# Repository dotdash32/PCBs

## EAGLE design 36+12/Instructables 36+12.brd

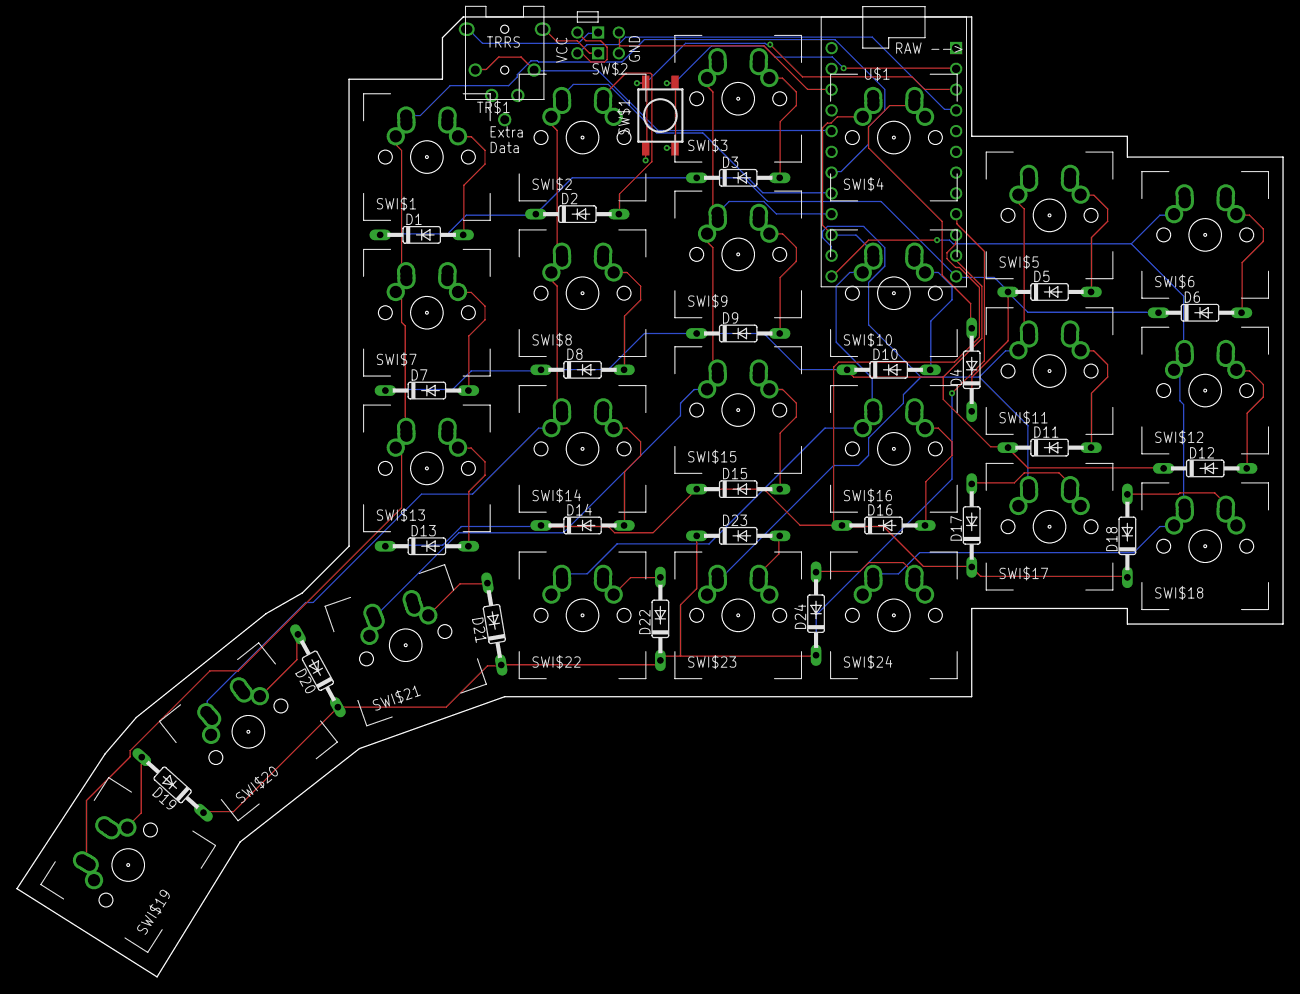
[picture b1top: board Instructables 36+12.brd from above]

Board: 2 copper layers, 154.9 x 117.5 mm, 52 parts (0 on the bottom side), 41 nets.

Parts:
D1, D2, D3, D4, D5, D6, D7, D8, D9, D10, D11, D12, D13, D14, D15, D16, D17, D18, D19, D20, D21, D22, D23, D24: 1N4148DO35-10; DO35-10
SW$1: RSTSWSMD; FLATSWT
SW$2: TRANSFERHOLEY; TRANSFER
SWI$1, SWI$2, SWI$3, SWI$4, SWI$5, SWI$6, SWI$7, SWI$8, SWI$9, SWI$10, SWI$11, SWI$12, SWI$13, SWI$14, SWI$15, SWI$16, SWI$17, SWI$18, SWI$19, SWI$20, SWI$21, SWI$22, SWI$23, SWI$24: MX/ALPSDOUBLESIDED; DOUBLED_MX/ALPS
TR$1: TRRSJACK
U$1: PROMICROUNDER; PROMICRO_UNDER

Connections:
unnamed: D13.A, SWI$13.RAL, SWI$13.RAR, SWI$13.RCL, SWI$13.RCR
unnamed: D1.A, SWI$1.RAL, SWI$1.RAR, SWI$1.RCL, SWI$1.RCR
unnamed: D2.A, SWI$2.RAL, SWI$2.RAR, SWI$2.RCL, SWI$2.RCR
unnamed: D3.A, SWI$3.RAL, SWI$3.RAR, SWI$3.RCL, SWI$3.RCR
unnamed: D4.A, SWI$4.RAL, SWI$4.RAR, SWI$4.RCL, SWI$4.RCR
unnamed: D5.A, SWI$5.RAL, SWI$5.RAR, SWI$5.RCL, SWI$5.RCR
unnamed: D6.A, SWI$6.RAL, SWI$6.RAR, SWI$6.RCL, SWI$6.RCR
unnamed: D7.A, SWI$7.RAL, SWI$7.RAR, SWI$7.RCL, SWI$7.RCR
unnamed: D8.A, SWI$8.RAL, SWI$8.RAR, SWI$8.RCL, SWI$8.RCR
unnamed: D9.A, SWI$9.RAL, SWI$9.RAR, SWI$9.RCL, SWI$9.RCR
unnamed: D10.A, SWI$10.RAL, SWI$10.RAR, SWI$10.RCL, SWI$10.RCR
unnamed: D11.A, SWI$11.RAL, SWI$11.RAR, SWI$11.RCL, SWI$11.RCR
unnamed: D12.A, SWI$12.RAL, SWI$12.RAR, SWI$12.RCL, SWI$12.RCR
unnamed: D14.A, SWI$14.RAL, SWI$14.RAR, SWI$14.RCL, SWI$14.RCR
unnamed: D15.A, SWI$15.RAL, SWI$15.RAR, SWI$15.RCL, SWI$15.RCR
unnamed: D16.A, SWI$16.RAL, SWI$16.RAR, SWI$16.RCL, SWI$16.RCR
unnamed: D17.A, SWI$17.RAL, SWI$17.RAR, SWI$17.RCL, SWI$17.RCR
unnamed: D18.A, SWI$18.RAL, SWI$18.RAR, SWI$18.RCL, SWI$18.RCR
unnamed: D19.A, SWI$19.RAL, SWI$19.RAR, SWI$19.RCL, SWI$19.RCR
unnamed: D20.A, SWI$20.RAL, SWI$20.RAR, SWI$20.RCL, SWI$20.RCR
unnamed: D21.A, SWI$21.RAL, SWI$21.RAR, SWI$21.RCL, SWI$21.RCR
unnamed: D22.A, SWI$22.RAL, SWI$22.RAR, SWI$22.RCL, SWI$22.RCR
unnamed: D23.A, SWI$23.RAL, SWI$23.RAR, SWI$23.RCL, SWI$23.RCR
unnamed: D24.A, SWI$24.RAL, SWI$24.RAR, SWI$24.RCL, SWI$24.RCR
unnamed: D1.C, D2.C, D3.C, D4.C, D5.C, D6.C, U$1.P$13
unnamed: D7.C, D8.C, D9.C, D10.C, D11.C, D12.C, U$1.P$14
unnamed: D13.C, D14.C, D15.C, D16.C, D17.C, D18.C, U$1.P$15
unnamed: D19.C, D20.C, D21.C, D22.C, D23.C, D24.C, U$1.P$16
unnamed: SWI$1.LAL, SWI$1.LAR, SWI$1.LCL, SWI$1.LCR, SWI$7.LAL, SWI$7.LAR, SWI$7.LCL, SWI$7.LCR, SWI$13.LAL, SWI$13.LAR, SWI$13.LCL, SWI$13.LCR, SWI$19.LAL, SWI$19.LAR, SWI$19.LCL, SWI$19.LCR, U$1.P$7
unnamed: SWI$2.LAL, SWI$2.LAR, SWI$2.LCL, SWI$2.LCR, SWI$8.LAL, SWI$8.LAR, SWI$8.LCL, SWI$8.LCR, SWI$14.LAL, SWI$14.LAR, SWI$14.LCL, SWI$14.LCR, SWI$20.LAL, SWI$20.LAR, SWI$20.LCL, SWI$20.LCR, U$1.P$8
unnamed: SWI$3.LAL, SWI$3.LAR, SWI$3.LCL, SWI$3.LCR, SWI$9.LAL, SWI$9.LAR, SWI$9.LCL, SWI$9.LCR, SWI$15.LAL, SWI$15.LAR, SWI$15.LCL, SWI$15.LCR, SWI$21.LAL, SWI$21.LAR, SWI$21.LCL, SWI$21.LCR, U$1.P$9
unnamed: SWI$4.LAL, SWI$4.LAR, SWI$4.LCL, SWI$4.LCR, SWI$10.LAL, SWI$10.LAR, SWI$10.LCL, SWI$10.LCR, SWI$16.LAL, SWI$16.LAR, SWI$16.LCL, SWI$16.LCR, SWI$22.LAL, SWI$22.LAR, SWI$22.LCL, SWI$22.LCR, U$1.P$10
unnamed: SWI$5.LAL, SWI$5.LAR, SWI$5.LCL, SWI$5.LCR, SWI$11.LAL, SWI$11.LAR, SWI$11.LCL, SWI$11.LCR, SWI$17.LAL, SWI$17.LAR, SWI$17.LCL, SWI$17.LCR, SWI$23.LAL, SWI$23.LAR, SWI$23.LCL, SWI$23.LCR, U$1.P$11
unnamed: SWI$6.LAL, SWI$6.LAR, SWI$6.LCL, SWI$6.LCR, SWI$12.LAL, SWI$12.LAR, SWI$12.LCL, SWI$12.LCR, SWI$18.LAL, SWI$18.LAR, SWI$18.LCL, SWI$18.LCR, SWI$24.LAL, SWI$24.LAR, SWI$24.LCL, SWI$24.LCR, U$1.P$12
unnamed: SW$1.P$1, SW$1.P$2, SW$1.P$5, SW$1.P$6, U$1.P$23
unnamed: SW$1.P$3, SW$1.P$4, SW$1.P$7, SW$1.P$8, U$1.P$22
unnamed: SW$2.GND1, SW$2.GND2, U$1.P$3
unnamed: SW$2.VCC1, SW$2.VCC2, U$1.P$21
unnamed: SW$2.IN1, TR$1.1B, TR$1.1T
unnamed: SW$2.IN4, TR$1.4B, TR$1.4T
unnamed: TR$1.2B, TR$1.2T, U$1.P$5

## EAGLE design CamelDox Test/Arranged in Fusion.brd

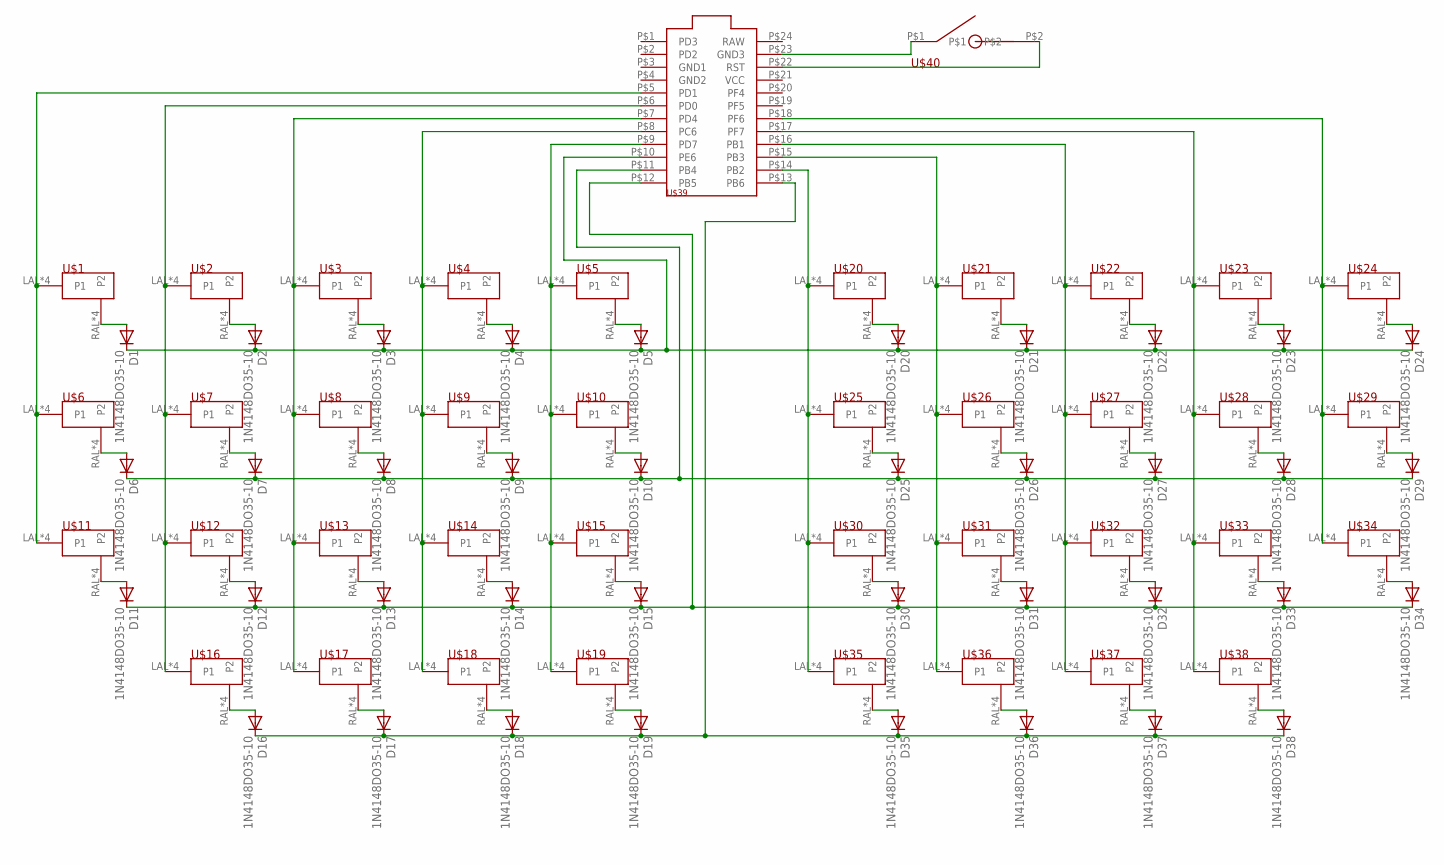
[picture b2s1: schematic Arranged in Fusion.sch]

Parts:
D1, D2, D3, D4, D5, D6, D7, D8, D9, D10, D11, D12, D13, D14, D15, D16, D17, D18, D19, D20, D21, D22, D23, D24, D25, D26, D27, D28, D29, D30, D31, D32, D33, D34, D35, D36, D37, D38: 1N4148DO35-10; DO35-10
U$1, U$2, U$3, U$4, U$5, U$6, U$7, U$8, U$9, U$10, U$11, U$12, U$13, U$14, U$15, U$16, U$17, U$18, U$19, U$20, U$21, U$22, U$23, U$24, U$25, U$26, U$27, U$28, U$29, U$30, U$31, U$32, U$33, U$34, U$35, U$36, U$37, U$38: MANDOUBLEONESIDED; MX/ALPS
U$39: PROMICRO
U$40: RSTSW; SKHL

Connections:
unnamed: D1.A, U$1.RAL (P2), U$1.RAR (P2), U$1.RCL (P2), U$1.RCR (P2)
unnamed: D2.A, U$2.RAL (P2), U$2.RAR (P2), U$2.RCL (P2), U$2.RCR (P2)
unnamed: D3.A, U$3.RAL (P2), U$3.RAR (P2), U$3.RCL (P2), U$3.RCR (P2)
unnamed: D4.A, U$4.RAL (P2), U$4.RAR (P2), U$4.RCL (P2), U$4.RCR (P2)
unnamed: D5.A, U$5.RAL (P2), U$5.RAR (P2), U$5.RCL (P2), U$5.RCR (P2)
unnamed: D1.C, D2.C, D3.C, D4.C, D5.C, D20.C, D21.C, D22.C, D23.C, D24.C, U$39.P$10 (PE6)
unnamed: D6.A, U$6.RAL (P2), U$6.RAR (P2), U$6.RCL (P2), U$6.RCR (P2)
unnamed: D7.A, U$7.RAL (P2), U$7.RAR (P2), U$7.RCL (P2), U$7.RCR (P2)
unnamed: D8.A, U$8.RAL (P2), U$8.RAR (P2), U$8.RCL (P2), U$8.RCR (P2)
unnamed: D9.A, U$9.RAL (P2), U$9.RAR (P2), U$9.RCL (P2), U$9.RCR (P2)
unnamed: D10.A, U$10.RAL (P2), U$10.RAR (P2), U$10.RCL (P2), U$10.RCR (P2)
unnamed: D11.A, U$11.RAL (P2), U$11.RAR (P2), U$11.RCL (P2), U$11.RCR (P2)
unnamed: D12.A, U$12.RAL (P2), U$12.RAR (P2), U$12.RCL (P2), U$12.RCR (P2)
unnamed: D13.A, U$13.RAL (P2), U$13.RAR (P2), U$13.RCL (P2), U$13.RCR (P2)
unnamed: D14.A, U$14.RAL (P2), U$14.RAR (P2), U$14.RCL (P2), U$14.RCR (P2)
unnamed: D15.A, U$15.RAL (P2), U$15.RAR (P2), U$15.RCL (P2), U$15.RCR (P2)
unnamed: D11.C, D12.C, D13.C, D14.C, D15.C, D30.C, D31.C, D32.C, D33.C, D34.C, U$39.P$12 (PB5)
unnamed: D16.A, U$16.RAL (P2), U$16.RAR (P2), U$16.RCL (P2), U$16.RCR (P2)
unnamed: D17.A, U$17.RAL (P2), U$17.RAR (P2), U$17.RCL (P2), U$17.RCR (P2)
unnamed: D18.A, U$18.RAL (P2), U$18.RAR (P2), U$18.RCL (P2), U$18.RCR (P2)
unnamed: D19.A, U$19.RAL (P2), U$19.RAR (P2), U$19.RCL (P2), U$19.RCR (P2)
unnamed: D16.C, D17.C, D18.C, D19.C, D35.C, D36.C, D37.C, D38.C, U$39.P$13 (PB6)
unnamed: D20.A, U$20.RAL (P2), U$20.RAR (P2), U$20.RCL (P2), U$20.RCR (P2)
unnamed: D21.A, U$21.RAL (P2), U$21.RAR (P2), U$21.RCL (P2), U$21.RCR (P2)
unnamed: D22.A, U$22.RAL (P2), U$22.RAR (P2), U$22.RCL (P2), U$22.RCR (P2)
unnamed: D23.A, U$23.RAL (P2), U$23.RAR (P2), U$23.RCL (P2), U$23.RCR (P2)
unnamed: D24.A, U$24.RAL (P2), U$24.RAR (P2), U$24.RCL (P2), U$24.RCR (P2)
unnamed: D25.A, U$25.RAL (P2), U$25.RAR (P2), U$25.RCL (P2), U$25.RCR (P2)
unnamed: D26.A, U$26.RAL (P2), U$26.RAR (P2), U$26.RCL (P2), U$26.RCR (P2)
unnamed: D27.A, U$27.RAL (P2), U$27.RAR (P2), U$27.RCL (P2), U$27.RCR (P2)
unnamed: D28.A, U$28.RAL (P2), U$28.RAR (P2), U$28.RCL (P2), U$28.RCR (P2)
unnamed: D29.A, U$29.RAL (P2), U$29.RAR (P2), U$29.RCL (P2), U$29.RCR (P2)
unnamed: D30.A, U$30.RAL (P2), U$30.RAR (P2), U$30.RCL (P2), U$30.RCR (P2)
unnamed: D31.A, U$31.RAL (P2), U$31.RAR (P2), U$31.RCL (P2), U$31.RCR (P2)
unnamed: D32.A, U$32.RAL (P2), U$32.RAR (P2), U$32.RCL (P2), U$32.RCR (P2)
unnamed: D33.A, U$33.RAL (P2), U$33.RAR (P2), U$33.RCL (P2), U$33.RCR (P2)
unnamed: D34.A, U$34.RAL (P2), U$34.RAR (P2), U$34.RCL (P2), U$34.RCR (P2)
unnamed: D35.A, U$35.RAL (P2), U$35.RAR (P2), U$35.RCL (P2), U$35.RCR (P2)
unnamed: D36.A, U$36.RAL (P2), U$36.RAR (P2), U$36.RCL (P2), U$36.RCR (P2)
unnamed: D37.A, U$37.RAL (P2), U$37.RAR (P2), U$37.RCL (P2), U$37.RCR (P2)
unnamed: D38.A, U$38.RAL (P2), U$38.RAR (P2), U$38.RCL (P2), U$38.RCR (P2)
unnamed: D6.C, D7.C, D8.C, D9.C, D10.C, D25.C, D26.C, D27.C, D28.C, D29.C, U$39.P$11 (PB4)
unnamed: U$1.LAL (P1), U$1.LAR (P1), U$1.LCL (P1), U$1.LCR (P1), U$6.LAL (P1), U$6.LAR (P1), U$6.LCL (P1), U$6.LCR (P1), U$11.LAL (P1), U$11.LAR (P1), U$11.LCL (P1), U$11.LCR (P1), U$39.P$5 (PD1)
unnamed: U$2.LAL (P1), U$2.LAR (P1), U$2.LCL (P1), U$2.LCR (P1), U$7.LAL (P1), U$7.LAR (P1), U$7.LCL (P1), U$7.LCR (P1), U$12.LAL (P1), U$12.LAR (P1), U$12.LCL (P1), U$12.LCR (P1), U$16.LAL (P1), U$16.LAR (P1), U$16.LCL (P1), U$16.LCR (P1), U$39.P$6 (PD0)
unnamed: U$3.LAL (P1), U$3.LAR (P1), U$3.LCL (P1), U$3.LCR (P1), U$8.LAL (P1), U$8.LAR (P1), U$8.LCL (P1), U$8.LCR (P1), U$13.LAL (P1), U$13.LAR (P1), U$13.LCL (P1), U$13.LCR (P1), U$17.LAL (P1), U$17.LAR (P1), U$17.LCL (P1), U$17.LCR (P1), U$39.P$7 (PD4)
unnamed: U$4.LAL (P1), U$4.LAR (P1), U$4.LCL (P1), U$4.LCR (P1), U$9.LAL (P1), U$9.LAR (P1), U$9.LCL (P1), U$9.LCR (P1), U$14.LAL (P1), U$14.LAR (P1), U$14.LCL (P1), U$14.LCR (P1), U$18.LAL (P1), U$18.LAR (P1), U$18.LCL (P1), U$18.LCR (P1), U$39.P$8 (PC6)
unnamed: U$5.LAL (P1), U$5.LAR (P1), U$5.LCL (P1), U$5.LCR (P1), U$10.LAL (P1), U$10.LAR (P1), U$10.LCL (P1), U$10.LCR (P1), U$15.LAL (P1), U$15.LAR (P1), U$15.LCL (P1), U$15.LCR (P1), U$19.LAL (P1), U$19.LAR (P1), U$19.LCL (P1), U$19.LCR (P1), U$39.P$9 (PD7)
unnamed: U$20.LAL (P1), U$20.LAR (P1), U$20.LCL (P1), U$20.LCR (P1), U$25.LAL (P1), U$25.LAR (P1), U$25.LCL (P1), U$25.LCR (P1), U$30.LAL (P1), U$30.LAR (P1), U$30.LCL (P1), U$30.LCR (P1), U$35.LAL (P1), U$35.LAR (P1), U$35.LCL (P1), U$35.LCR (P1), U$39.P$14 (PB2)
unnamed: U$21.LAL (P1), U$21.LAR (P1), U$21.LCL (P1), U$21.LCR (P1), U$26.LAL (P1), U$26.LAR (P1), U$26.LCL (P1), U$26.LCR (P1), U$31.LAL (P1), U$31.LAR (P1), U$31.LCL (P1), U$31.LCR (P1), U$36.LAL (P1), U$36.LAR (P1), U$36.LCL (P1), U$36.LCR (P1), U$39.P$15 (PB3)
unnamed: U$22.LAL (P1), U$22.LAR (P1), U$22.LCL (P1), U$22.LCR (P1), U$27.LAL (P1), U$27.LAR (P1), U$27.LCL (P1), U$27.LCR (P1), U$32.LAL (P1), U$32.LAR (P1), U$32.LCL (P1), U$32.LCR (P1), U$37.LAL (P1), U$37.LAR (P1), U$37.LCL (P1), U$37.LCR (P1), U$39.P$16 (PB1)
unnamed: U$23.LAL (P1), U$23.LAR (P1), U$23.LCL (P1), U$23.LCR (P1), U$28.LAL (P1), U$28.LAR (P1), U$28.LCL (P1), U$28.LCR (P1), U$33.LAL (P1), U$33.LAR (P1), U$33.LCL (P1), U$33.LCR (P1), U$38.LAL (P1), U$38.LAR (P1), U$38.LCL (P1), U$38.LCR (P1), U$39.P$17 (PF7)
unnamed: U$24.LAL (P1), U$24.LAR (P1), U$24.LCL (P1), U$24.LCR (P1), U$29.LAL (P1), U$29.LAR (P1), U$29.LCL (P1), U$29.LCR (P1), U$34.LAL (P1), U$34.LAR (P1), U$34.LCL (P1), U$34.LCR (P1), U$39.P$18 (PF6)
unnamed: U$39.P$23 (GND3), U$40.P$1
unnamed: U$39.P$22 (RST), U$40.P$2

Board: 2 copper layers, 78 parts (0 on the bottom side), 54 nets, no tracks yet.

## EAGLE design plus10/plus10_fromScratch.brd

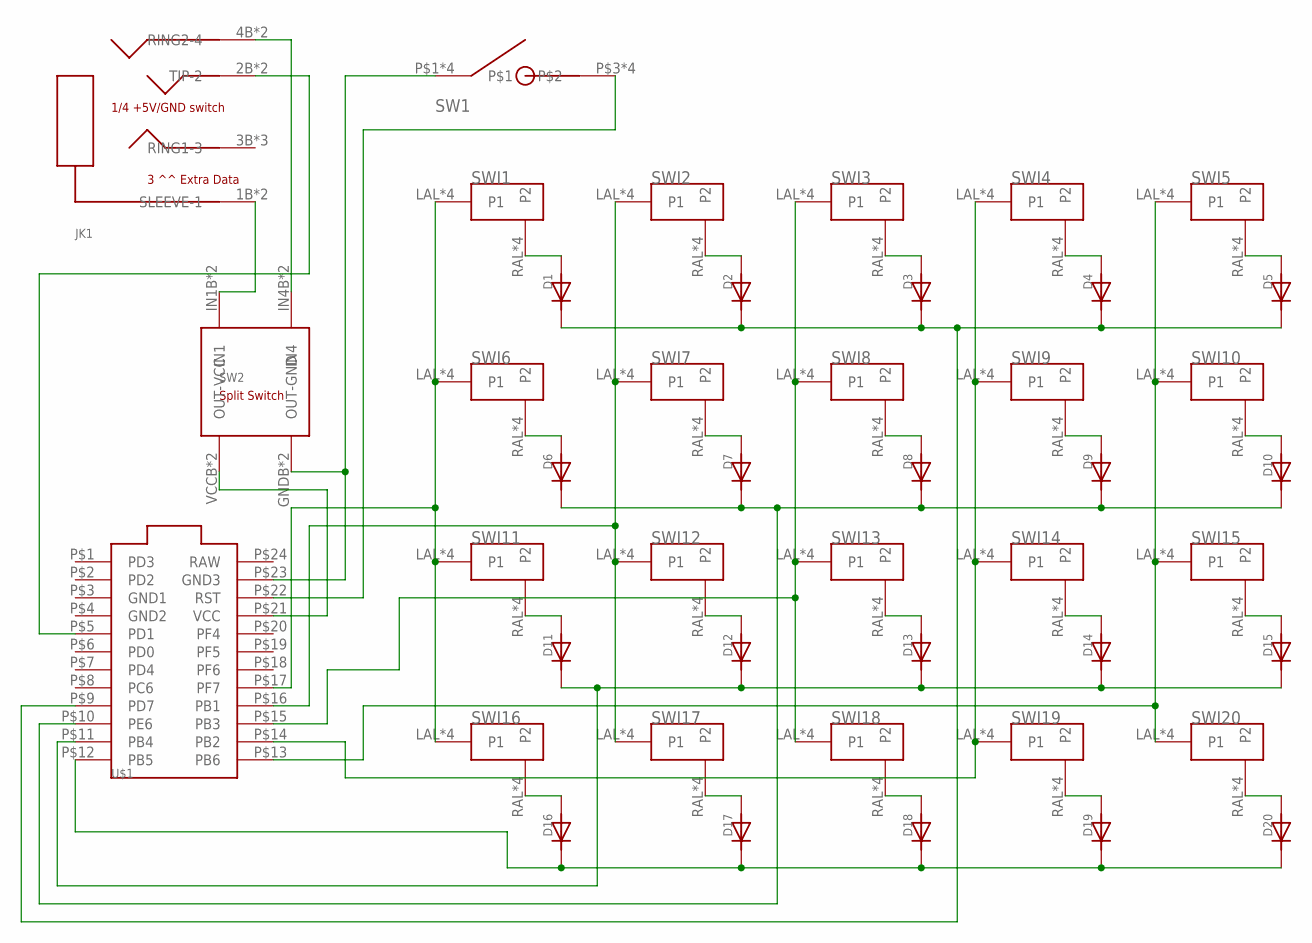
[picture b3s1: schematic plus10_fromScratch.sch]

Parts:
D1, D2, D3, D4, D5, D6, D7, D8, D9, D10, D11, D12, D13, D14, D15, D16, D17, D18, D19, D20: DIODE; DIODE_COMBO
JK1: TRRSJACK
SW1: RSTSWSMD; FLATSWT
SW2: TRANSFERPADDY; TRANSFER_PADS
SWI1, SWI2, SWI3, SWI4, SWI5, SWI6, SWI7, SWI8, SWI9, SWI10, SWI11, SWI12, SWI13, SWI14, SWI15, SWI16, SWI17, SWI18, SWI19, SWI20: MX/ALPSDOUBLESIDED; DOUBLED_MX/ALPS
U$1: PROMICROUNDER; PROMICRO_UNDER

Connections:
unnamed: D1.ANOSB (AN), D1.ANOST (AN), D1.ANOT (AN), SWI1.RAL (P2), SWI1.RAR (P2), SWI1.RCL (P2), SWI1.RCR (P2)
unnamed: SWI4.LAL (P1), SWI4.LAR (P1), SWI4.LCL (P1), SWI4.LCR (P1), SWI9.LAL (P1), SWI9.LAR (P1), SWI9.LCL (P1), SWI9.LCR (P1), SWI14.LAL (P1), SWI14.LAR (P1), SWI14.LCL (P1), SWI14.LCR (P1), SWI19.LAL (P1), SWI19.LAR (P1), SWI19.LCL (P1), SWI19.LCR (P1), U$1.P$14 (PB2)
unnamed: SWI3.LAL (P1), SWI3.LAR (P1), SWI3.LCL (P1), SWI3.LCR (P1), SWI8.LAL (P1), SWI8.LAR (P1), SWI8.LCL (P1), SWI8.LCR (P1), SWI13.LAL (P1), SWI13.LAR (P1), SWI13.LCL (P1), SWI13.LCR (P1), SWI18.LAL (P1), SWI18.LAR (P1), SWI18.LCL (P1), SWI18.LCR (P1), U$1.P$15 (PB3)
unnamed: SWI5.LAL (P1), SWI5.LAR (P1), SWI5.LCL (P1), SWI5.LCR (P1), SWI10.LAL (P1), SWI10.LAR (P1), SWI10.LCL (P1), SWI10.LCR (P1), SWI15.LAL (P1), SWI15.LAR (P1), SWI15.LCL (P1), SWI15.LCR (P1), SWI20.LAL (P1), SWI20.LAR (P1), SWI20.LCL (P1), SWI20.LCR (P1), U$1.P$13 (PB6)
unnamed: D2.ANOSB (AN), D2.ANOST (AN), D2.ANOT (AN), SWI2.RAL (P2), SWI2.RAR (P2), SWI2.RCL (P2), SWI2.RCR (P2)
unnamed: D3.ANOSB (AN), D3.ANOST (AN), D3.ANOT (AN), SWI3.RAL (P2), SWI3.RAR (P2), SWI3.RCL (P2), SWI3.RCR (P2)
unnamed: D4.ANOSB (AN), D4.ANOST (AN), D4.ANOT (AN), SWI4.RAL (P2), SWI4.RAR (P2), SWI4.RCL (P2), SWI4.RCR (P2)
unnamed: D5.ANOSB (AN), D5.ANOST (AN), D5.ANOT (AN), SWI5.RAL (P2), SWI5.RAR (P2), SWI5.RCL (P2), SWI5.RCR (P2)
unnamed: D6.ANOSB (AN), D6.ANOST (AN), D6.ANOT (AN), SWI6.RAL (P2), SWI6.RAR (P2), SWI6.RCL (P2), SWI6.RCR (P2)
unnamed: D7.ANOSB (AN), D7.ANOST (AN), D7.ANOT (AN), SWI7.RAL (P2), SWI7.RAR (P2), SWI7.RCL (P2), SWI7.RCR (P2)
unnamed: D8.ANOSB (AN), D8.ANOST (AN), D8.ANOT (AN), SWI8.RAL (P2), SWI8.RAR (P2), SWI8.RCL (P2), SWI8.RCR (P2)
unnamed: D9.ANOSB (AN), D9.ANOST (AN), D9.ANOT (AN), SWI9.RAL (P2), SWI9.RAR (P2), SWI9.RCL (P2), SWI9.RCR (P2)
unnamed: D10.ANOSB (AN), D10.ANOST (AN), D10.ANOT (AN), SWI10.RAL (P2), SWI10.RAR (P2), SWI10.RCL (P2), SWI10.RCR (P2)
unnamed: D11.ANOSB (AN), D11.ANOST (AN), D11.ANOT (AN), SWI11.RAL (P2), SWI11.RAR (P2), SWI11.RCL (P2), SWI11.RCR (P2)
unnamed: D12.ANOSB (AN), D12.ANOST (AN), D12.ANOT (AN), SWI12.RAL (P2), SWI12.RAR (P2), SWI12.RCL (P2), SWI12.RCR (P2)
unnamed: D13.ANOSB (AN), D13.ANOST (AN), D13.ANOT (AN), SWI13.RAL (P2), SWI13.RAR (P2), SWI13.RCL (P2), SWI13.RCR (P2)
unnamed: D14.ANOSB (AN), D14.ANOST (AN), D14.ANOT (AN), SWI14.RAL (P2), SWI14.RAR (P2), SWI14.RCL (P2), SWI14.RCR (P2)
unnamed: D15.ANOSB (AN), D15.ANOST (AN), D15.ANOT (AN), SWI15.RAL (P2), SWI15.RAR (P2), SWI15.RCL (P2), SWI15.RCR (P2)
unnamed: D16.ANOSB (AN), D16.ANOST (AN), D16.ANOT (AN), SWI16.RAL (P2), SWI16.RAR (P2), SWI16.RCL (P2), SWI16.RCR (P2)
unnamed: D17.ANOSB (AN), D17.ANOST (AN), D17.ANOT (AN), SWI17.RAL (P2), SWI17.RAR (P2), SWI17.RCL (P2), SWI17.RCR (P2)
unnamed: D11.CATSB (CAT), D11.CATST (CAT), D11.CATT (CAT), D12.CATSB (CAT), D12.CATST (CAT), D12.CATT (CAT), D13.CATSB (CAT), D13.CATST (CAT), D13.CATT (CAT), D14.CATSB (CAT), D14.CATST (CAT), D14.CATT (CAT), D15.CATSB (CAT), D15.CATST (CAT), D15.CATT (CAT), U$1.P$11 (PB4)
unnamed: D6.CATSB (CAT), D6.CATST (CAT), D6.CATT (CAT), D7.CATSB (CAT), D7.CATST (CAT), D7.CATT (CAT), D8.CATSB (CAT), D8.CATST (CAT), D8.CATT (CAT), D9.CATSB (CAT), D9.CATST (CAT), D9.CATT (CAT), D10.CATSB (CAT), D10.CATST (CAT), D10.CATT (CAT), U$1.P$10 (PE6)
unnamed: D18.ANOSB (AN), D18.ANOST (AN), D18.ANOT (AN), SWI18.RAL (P2), SWI18.RAR (P2), SWI18.RCL (P2), SWI18.RCR (P2)
unnamed: D16.CATSB (CAT), D16.CATST (CAT), D16.CATT (CAT), D17.CATSB (CAT), D17.CATST (CAT), D17.CATT (CAT), D18.CATSB (CAT), D18.CATST (CAT), D18.CATT (CAT), D19.CATSB (CAT), D19.CATST (CAT), D19.CATT (CAT), D20.CATSB (CAT), D20.CATST (CAT), D20.CATT (CAT), U$1.P$12 (PB5)
unnamed: SWI1.LAL (P1), SWI1.LAR (P1), SWI1.LCL (P1), SWI1.LCR (P1), SWI6.LAL (P1), SWI6.LAR (P1), SWI6.LCL (P1), SWI6.LCR (P1), SWI11.LAL (P1), SWI11.LAR (P1), SWI11.LCL (P1), SWI11.LCR (P1), SWI16.LAL (P1), SWI16.LAR (P1), SWI16.LCL (P1), SWI16.LCR (P1), U$1.P$17 (PF7)
unnamed: SWI2.LAL (P1), SWI2.LAR (P1), SWI2.LCL (P1), SWI2.LCR (P1), SWI7.LAL (P1), SWI7.LAR (P1), SWI7.LCL (P1), SWI7.LCR (P1), SWI12.LAL (P1), SWI12.LAR (P1), SWI12.LCL (P1), SWI12.LCR (P1), SWI17.LAL (P1), SWI17.LAR (P1), SWI17.LCL (P1), SWI17.LCR (P1), U$1.P$16 (PB1)
unnamed: JK1.1B (SLEEVE-1), JK1.1T (SLEEVE-1), SW2.IN1B (IN1), SW2.IN1T (IN1)
unnamed: JK1.4B (RING2-4), JK1.4T (RING2-4), SW2.IN4B (IN4), SW2.IN4T (IN4)
unnamed: JK1.2B (TIP-2), JK1.2T (TIP-2), U$1.P$5 (PD1)
unnamed: D1.CATSB (CAT), D1.CATST (CAT), D1.CATT (CAT), D2.CATSB (CAT), D2.CATST (CAT), D2.CATT (CAT), D3.CATSB (CAT), D3.CATST (CAT), D3.CATT (CAT), D4.CATSB (CAT), D4.CATST (CAT), D4.CATT (CAT), D5.CATSB (CAT), D5.CATST (CAT), D5.CATT (CAT), U$1.P$9 (PD7)
unnamed: D19.ANOSB (AN), D19.ANOST (AN), D19.ANOT (AN), SWI19.RAL (P2), SWI19.RAR (P2), SWI19.RCL (P2), SWI19.RCR (P2)
unnamed: D20.ANOSB (AN), D20.ANOST (AN), D20.ANOT (AN), SWI20.RAL (P2), SWI20.RAR (P2), SWI20.RCL (P2), SWI20.RCR (P2)
unnamed: SW2.VCCB (OUT-VCC), SW2.VCCT (OUT-VCC), U$1.P$21 (VCC)
unnamed: SW1.P$1, SW1.P$2, SW1.P$5, SW1.P$6, SW2.GNDB (OUT-GND), SW2.GNDT (OUT-GND), U$1.P$23 (GND3)
unnamed: SW1.P$3, SW1.P$4, SW1.P$7, SW1.P$8, U$1.P$22 (RST)

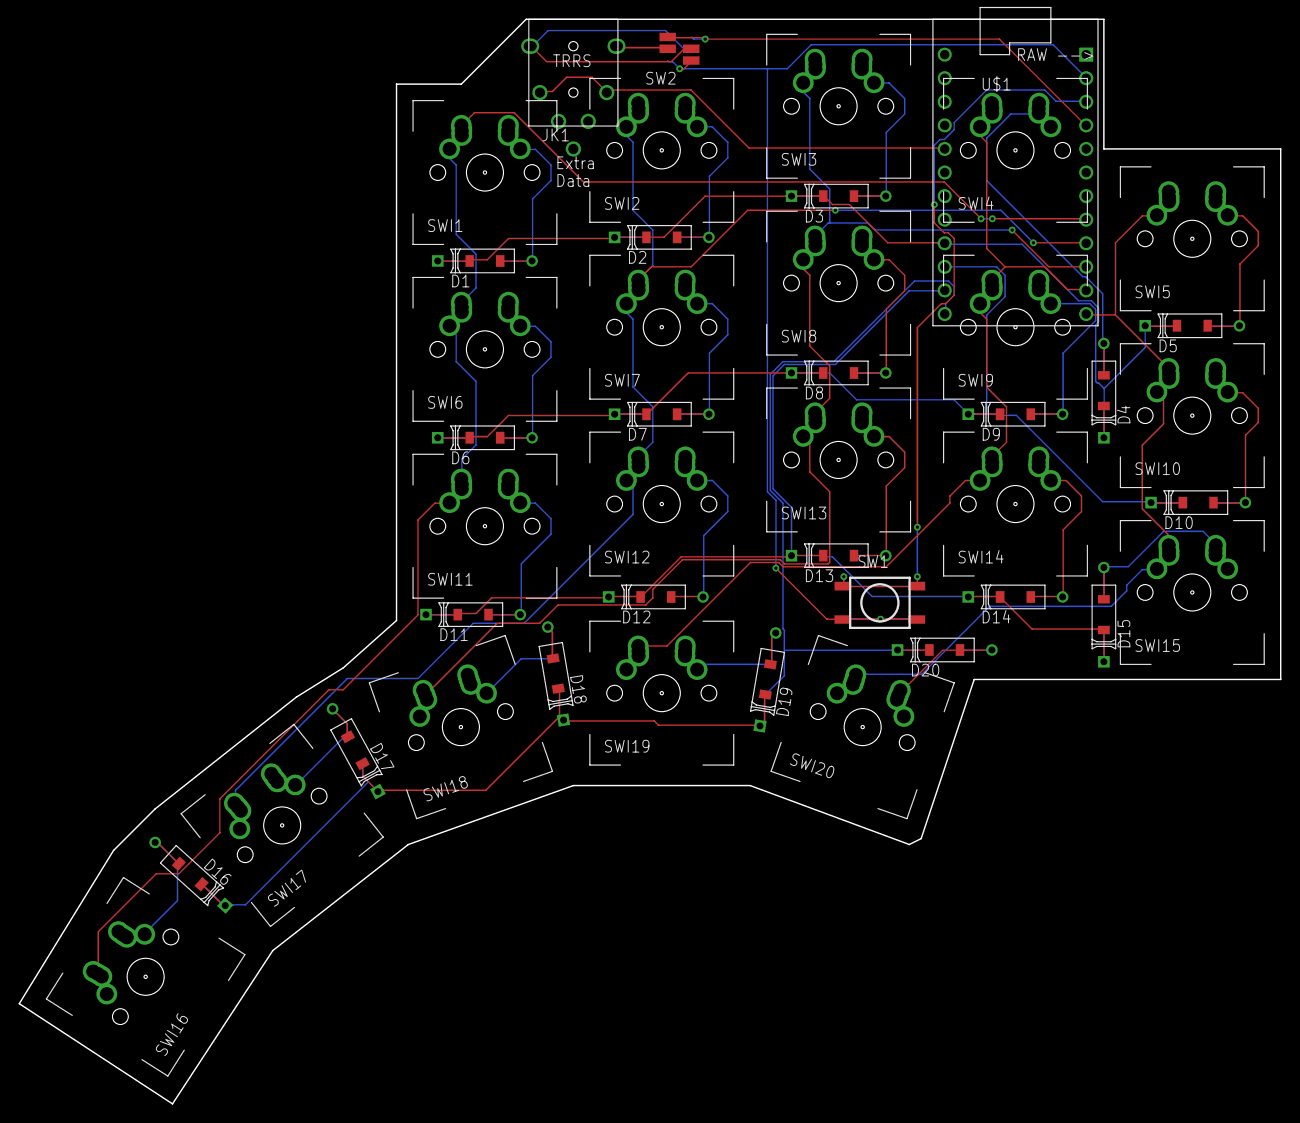
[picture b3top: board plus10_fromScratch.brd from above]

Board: 2 copper layers, 135.9 x 116.8 mm, 44 parts (0 on the bottom side), 35 nets.

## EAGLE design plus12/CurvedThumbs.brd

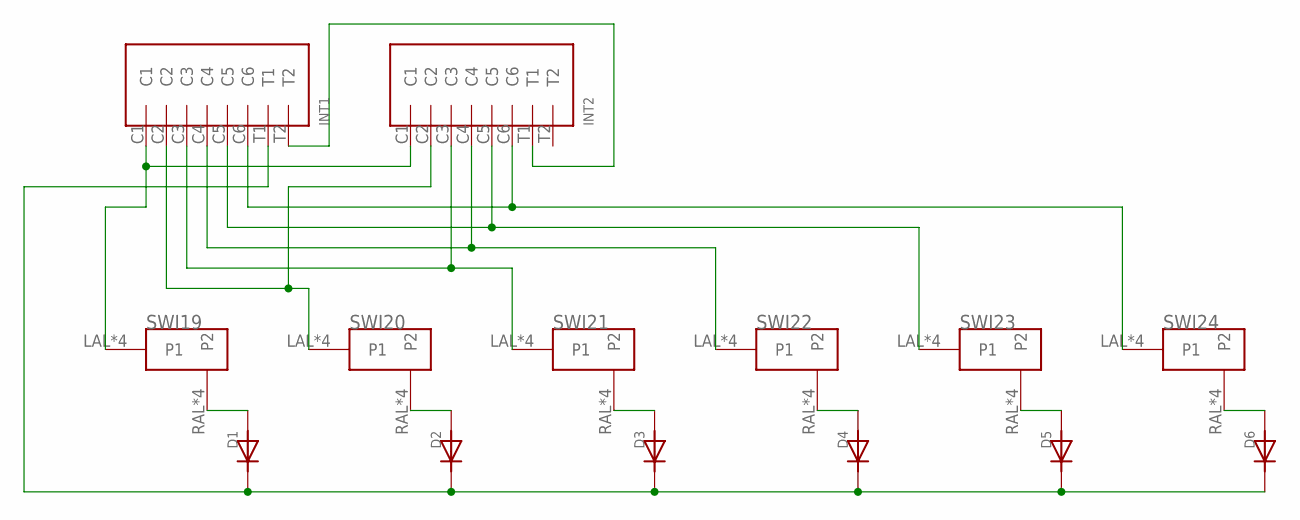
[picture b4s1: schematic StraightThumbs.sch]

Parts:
D1, D2, D3, D4, D5, D6: DIODE; DIODE_COMBO
INT1, INT2: INTRCNNT
SWI19, SWI20, SWI21, SWI22, SWI23, SWI24: MX/ALPSDOUBLESIDED; DOUBLED_MX/ALPS

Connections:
unnamed: D1.ANOSB (AN), D1.ANOST (AN), D1.ANOT (AN), SWI19.RAL (P2), SWI19.RAR (P2), SWI19.RCL (P2), SWI19.RCR (P2)
unnamed: D2.ANOSB (AN), D2.ANOST (AN), D2.ANOT (AN), SWI20.RAL (P2), SWI20.RAR (P2), SWI20.RCL (P2), SWI20.RCR (P2)
unnamed: D3.ANOSB (AN), D3.ANOST (AN), D3.ANOT (AN), SWI21.RAL (P2), SWI21.RAR (P2), SWI21.RCL (P2), SWI21.RCR (P2)
unnamed: D4.ANOSB (AN), D4.ANOST (AN), D4.ANOT (AN), SWI22.RAL (P2), SWI22.RAR (P2), SWI22.RCL (P2), SWI22.RCR (P2)
unnamed: D5.ANOSB (AN), D5.ANOST (AN), D5.ANOT (AN), SWI23.RAL (P2), SWI23.RAR (P2), SWI23.RCL (P2), SWI23.RCR (P2)
unnamed: D6.ANOSB (AN), D6.ANOST (AN), D6.ANOT (AN), SWI24.RAL (P2), SWI24.RAR (P2), SWI24.RCL (P2), SWI24.RCR (P2)
unnamed: INT1.C1, INT2.C1, SWI19.LAL (P1), SWI19.LAR (P1), SWI19.LCL (P1), SWI19.LCR (P1)
unnamed: INT1.C2, INT2.C2, SWI20.LAL (P1), SWI20.LAR (P1), SWI20.LCL (P1), SWI20.LCR (P1)
unnamed: INT1.C3, INT2.C3, SWI21.LAL (P1), SWI21.LAR (P1), SWI21.LCL (P1), SWI21.LCR (P1)
unnamed: INT1.C4, INT2.C4, SWI22.LAL (P1), SWI22.LAR (P1), SWI22.LCL (P1), SWI22.LCR (P1)
unnamed: INT1.C5, INT2.C5, SWI23.LAL (P1), SWI23.LAR (P1), SWI23.LCL (P1), SWI23.LCR (P1)
unnamed: INT1.C6, INT2.C6, SWI24.LAL (P1), SWI24.LAR (P1), SWI24.LCL (P1), SWI24.LCR (P1)
unnamed: D1.CATSB (CAT), D1.CATST (CAT), D1.CATT (CAT), D2.CATSB (CAT), D2.CATST (CAT), D2.CATT (CAT), D3.CATSB (CAT), D3.CATST (CAT), D3.CATT (CAT), D4.CATSB (CAT), D4.CATST (CAT), D4.CATT (CAT), D5.CATSB (CAT), D5.CATST (CAT), D5.CATT (CAT), D6.CATSB (CAT), D6.CATST (CAT), D6.CATT (CAT), INT1.T1
unnamed: INT1.T2, INT2.T1

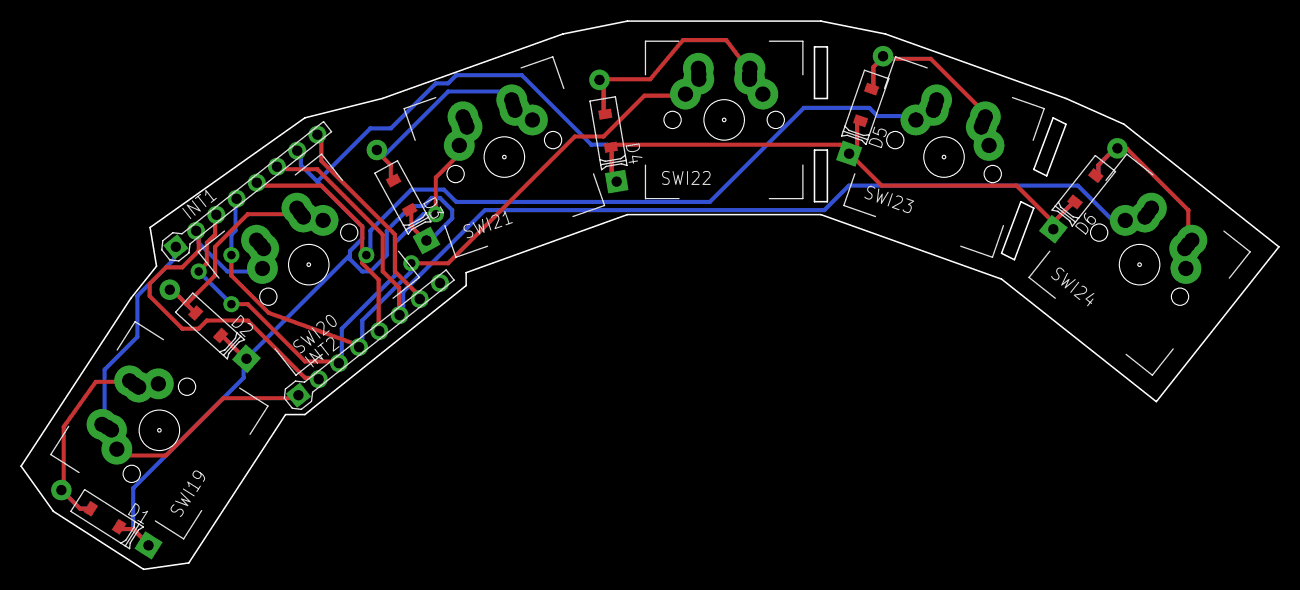
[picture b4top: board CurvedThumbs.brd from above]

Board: 2 copper layers, 123.8 x 54.0 mm, 14 parts (0 on the bottom side), 14 nets.
